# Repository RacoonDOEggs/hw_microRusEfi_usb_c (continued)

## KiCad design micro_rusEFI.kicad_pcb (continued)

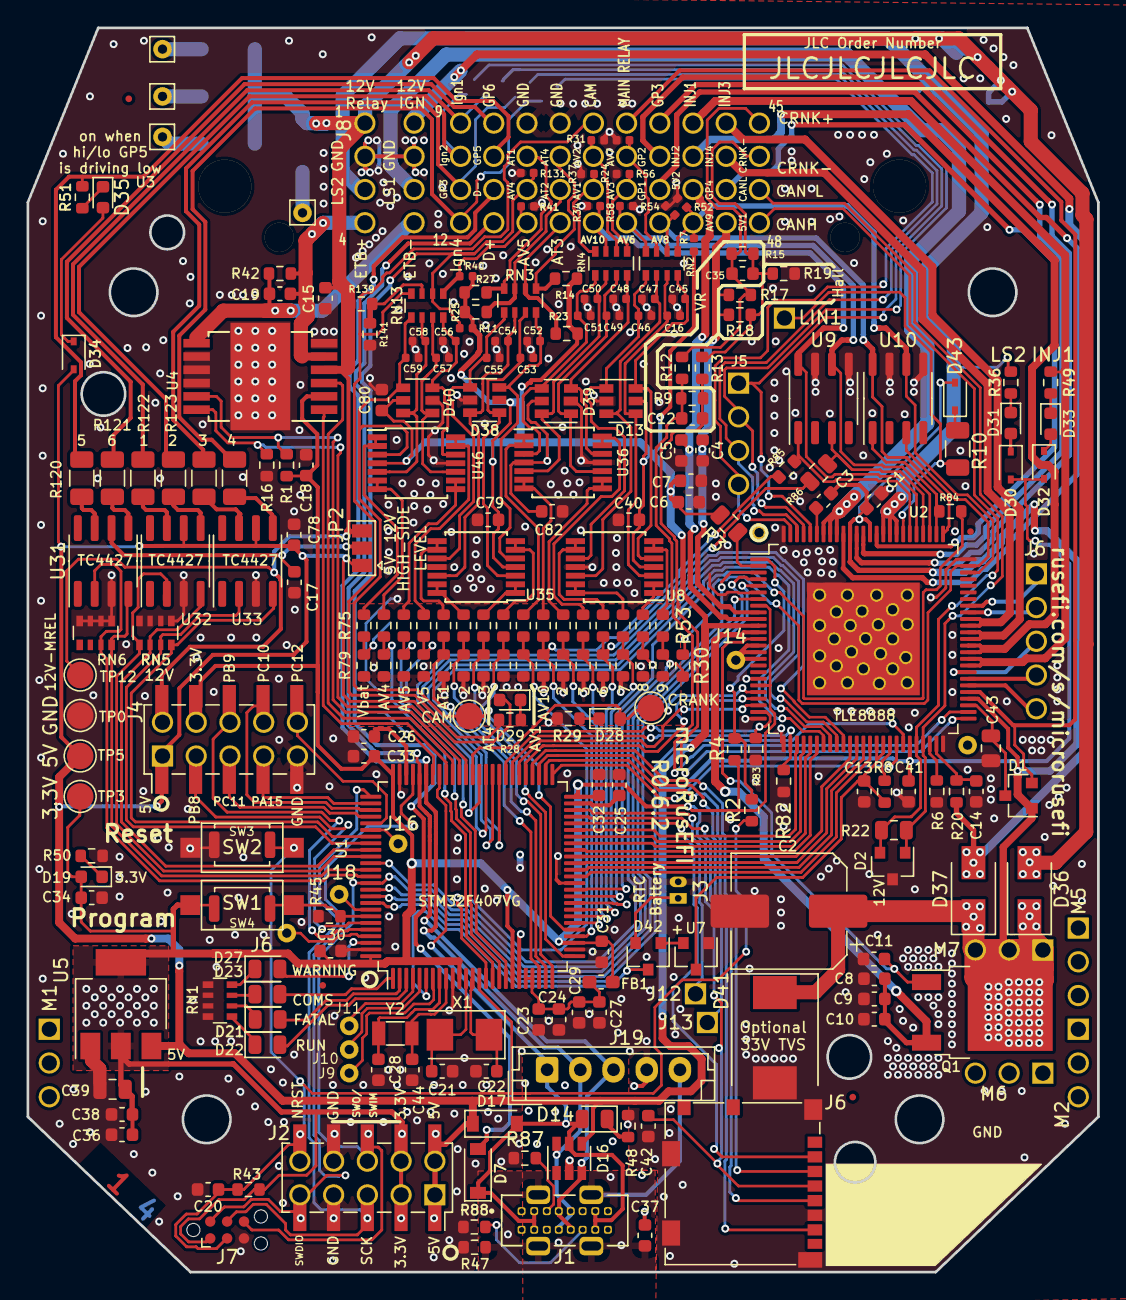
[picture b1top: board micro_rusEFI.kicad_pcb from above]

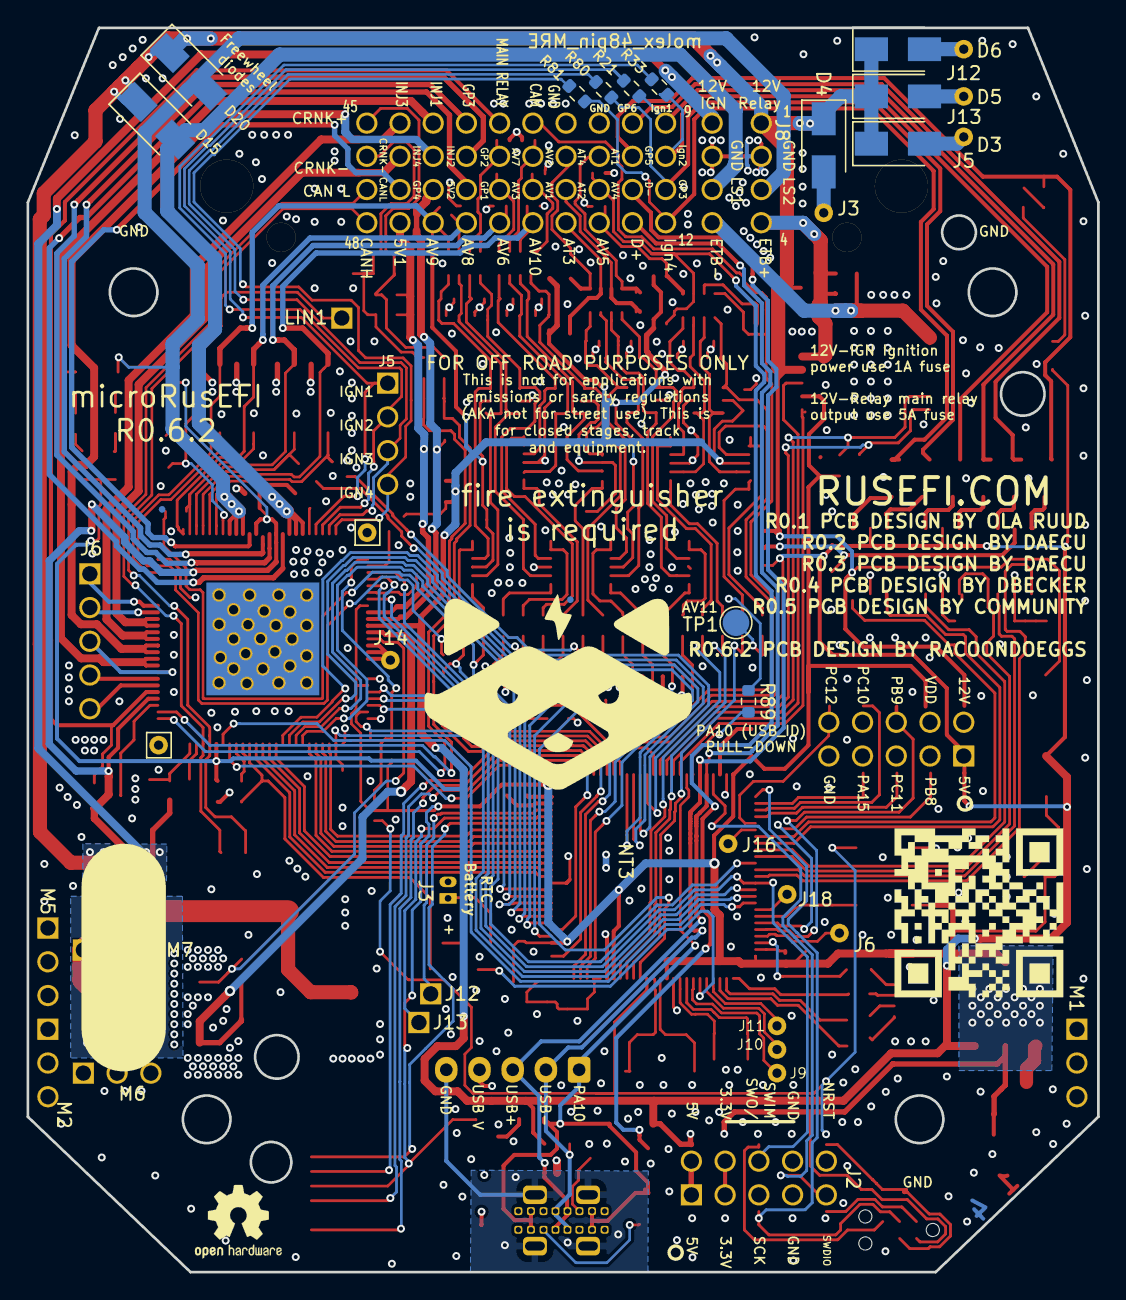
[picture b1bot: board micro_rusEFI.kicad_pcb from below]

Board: 4 copper layers, 80.6 x 93.7 mm, 257 parts (20 on the bottom side), 227 nets.

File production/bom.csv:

Designator,Footprint,Quantity,Value,LCSC Part #
"C1, C10, C13, C14, C15, C17, C18, C24, C30, C31, C32, C33, C34, C37, C38, C42, C6, C78",0603,18,100nF,C14663
"C11, C3",0603,2,4.7nF,C53987
"C12, C35",0603,2,1nF,C1588
"C16, C45, C46, C47, C48, C49, C50, C51, C52, C53, C54, C55, C56, C57, C58, C59",0402,16,100nF,C1525
"C19, C20, C29, C40, C79, C80, C82",0603,7,10nF,C57112
C2,CP_Elec_8x10.5,1,100UF 50V,C134515
"C21, C22",0603,2,18pF,C1647
"C23, C27, C36",0603,3,1uF,C15849
"C25, C26, C41",0603,3,2.2uF,C23630
"C28, C44",0603,2,6.8pF,C1679
C39,0805,1,22uF,C59461
"C4, C5",0603,2,470nF,C1623
C43,0805,1,22uF 25V,C45783
"C7, C8, C9",0603,3,10uF,C19702
"D1, D42",SOT-23,2,BAV70,C82479
"D13, D16, D38, D39, D40",SOT-23-6,5,SRV05-4,C85364
"D14, D22",0805,2,LED-GREEN,C2297
"D15, D20, D3, D36, D37, D4, D5, D6",D_SMA,8,SS54,C22452
"D17, D7",D_SOD-123,2,B5819W,C8598
"D19, D28, D29, D31, D33, D35",0603,6,LED-RED,C2286
D2,SOT-23,1,PESD1CAN-UX,C152727
D21,0805,1,LED-RED,C84256
D23,0805,1,LED-BLUE,C2293
D27,0805,1,LED-YELLOW,C2296
"D30, D32, D34, D43",D_SOD-323,4,1N4148WS,C2128
D41,D_SMC,1,SM15T33C,C133707
FB1,0603,1,FILTER,C1034
"FID1, FID2, FID3, FID4, FID5, FID6",Fiducial_0.5mm_Mask1mm,6,Fiducial,
G1,Off_Road_Disclaimer,1,Disclaimer,
J1,CUI_UJ20-C-V-C-2-SMT-TR,1,UJ20-C-V-C-2-SMT-TR,
"J12, J13, J15, J17, J3, J5",Pin_D0.7mm_L6.5mm_W1.8mm_FlatFork,6,Conn_01x01,
J19,JST_EH_B5B-EH-A_1x05_P2.50mm_Vertical,1,Conn_01x06,
J2,PinSocket_2x05_P2.54mm_Vertical_SMD,1,Conn_02x05_Odd_Even,
J4,PinHeader_2x05_P2.54mm_Vertical_SMD,1,Conn_02x05_Counter_Clockwise,
J6,microSD_HC_Molex_104031-0811,1,Micro_SD_Card_Det,C585350
J7,Tag-Connect_TC2030-IDC-NL_2x03_P1.27mm_Vertical,1,TC2030,
JP2,SolderJumper-3_P1.3mm_Open_Pad1.0x1.5mm,1,High side voltage 5V 12V,
LOGO1,OSHW-Logo2_7.3x6mm_SilkScreen,1,DNP,
LOGO3,MRE_QR_code,1,LOGO,
"NT1, NT2",Net-Tie_2_8.5mil,2,Net-Tie_2,
NT3,NetTie-2_SMD_Pad0.5mm,1,Analog Ground Net Tie,
Q1,TO-252-2,1,IPD30N06S2L-23,C3010
"R1, R12, R13, R141, R16, R38, R39, R4, R43, R44, R45, R46, R6, R60, R61, R62, R63, R68, R69, R70, R71, R76, R77, R78, R79, R89",0603,26,10K,C25804
R10,1206,1,1k,C4410
"R11, R40, R7",0402,3,DNP,
"R120, R121, R122, R123, R124, R125",1206,6,100,C17901
"R131, R24, R31, R34, R37, R41, R52, R54, R56, R58",0402,10,470K,C25790
R139,0603,1,39k,C23153
"R14, R20, R23, R25, R27",0603,5,2.7k,C13167
"R15, R17, R18, R19",0603,4,DNP,
R2,0603,1,0R DNP,
"R21, R30, R33, R8, R80, R81, R84",0603,7,0R,C21189
R22,0805,1,120,C17437
"R26, R32, R35, R5, R57, R59, R64, R65, R66, R67, R72, R73, R74, R75",0603,14,6.8K,C23212
"R28, R48",0603,2,2.2k,C4190
"R29, R36, R49, R50, R51",0603,5,1k,C21190
R3,0805,1,10K,C17414
"R42, R82, R83",0603,3,4.7K,C23162
R47,0603,1,100K,C25803
"R53, R55",0603,2,6.8K,
R85,0603,1,0R,
R86,0805,1,0R,
"R87, R88",0603,2,5.1k,C21190
R9,0603,1,4.7K,DNP
RN1,R_Array_Convex_4x0603,1,1k,C20197
"RN13, RN2, RN3, RN4, RN5, RN6",R_Array_Convex_4x0603,6,10k,C29718
"SW1, SW2",SW_SPST_CK_RS282G05A3,2,SW_Push,C398054
"SW3, SW4",SW_Push_SPST_NO_Alps_SKRK,2,SW_Push,
"TP0, TP3",TestPoint_Pad_D2.0mm,2,GND,
"TP1, TP2, TP4",TestPoint_Pad_D2.0mm,3,TP,
"TP12, TP5",TestPoint_Pad_D2.0mm,2,5V,
U1,LQFP-100_14x14mm_P0.5mm,1,STM32F427VGT6,C117815
"U10, U9",SO-8_3.9x4.9mm_P1.27mm,2,VNLD5090,C377942
U2,LQFP-100_14x14mm_P0.5mm_THERMAL,1,TLE8888QK,
U3,Molex_48_MRE,1,molex_48pin_MRE,
"U31, U32, U33",SOIC-8_3.9x4.9mm_P1.27mm,3,MIC4427,C144205
"U35, U36, U46, U8",TSSOP-14_4.4x5mm_P0.65mm,4,MCP6004,C248577
U4,Infineon_PG-DSO-12-11,1,TLE9201SG,C112633
U5,SOT-223-3_TabPin2,1,LM1117-3.3,C6186
U7,SOT-23,1,XC6206 3.3V,C5446
X1,Crystal_SMD_5032-2Pin_5.0x3.2mm,1,8MHz 20pF,C115962
Y2,Crystal_SMD_3215-2Pin_3.2x1.5mm,1,32768 Hz,C32346

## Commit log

2025-06-16 replaces micro b connector by usb-c
2025-06-18 Impedence controlled USB traces
2025-06-19 widened usb trace to further reduce impedence
2025-06-24 completed board, created BOM
2025-06-24 adjusted BOM and created production files
